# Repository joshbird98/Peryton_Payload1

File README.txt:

Team Peryton - Payload

This is internal documentation for the team, however I will publish proper open-source documentation in the future.

* For our actual flight, we opted to replace the GPS circuitry with a loud siren. This gave us a much mre reliable
and robust recovery mechanism. Whislt the hardware schematics show the GPS and LoRa system, no software has
been published.

Our payload acts as both rocket recovery mechanism, and data acquisition. It logs pressure, temperature and 9DoF
motion measurements to a microSD card, at 50 [Hz]. Power it with a LiHV cell, preferably 450mAh.
Sensors used are the BMP280 and MPU9250, many open-source libraries already exist for these ICs.
An ATMEGA328P communicates to the sensors in I2C mode, and to the microSD card in SPI mode.

As well as the hardware and software, I've also written a python script for quick analysis of flight data, useful 
for when you're still in the field. Results from our rocketry flight are also included as an example of what
the payload has achieved.

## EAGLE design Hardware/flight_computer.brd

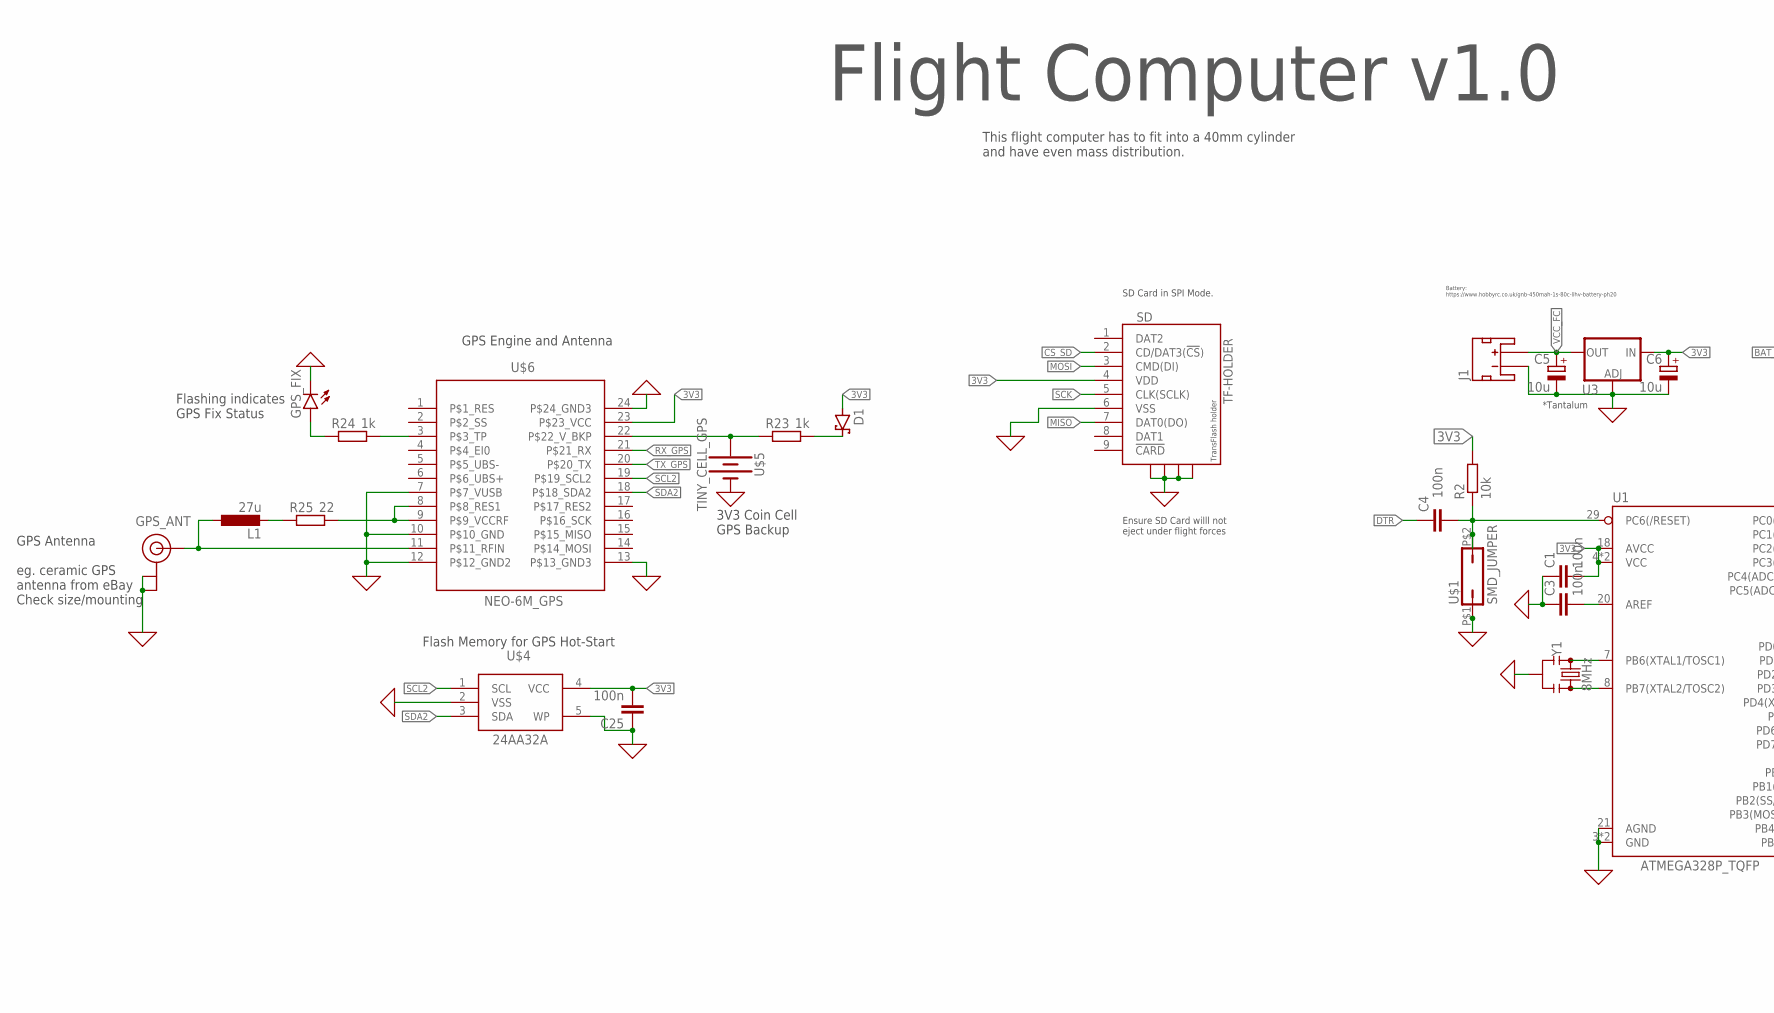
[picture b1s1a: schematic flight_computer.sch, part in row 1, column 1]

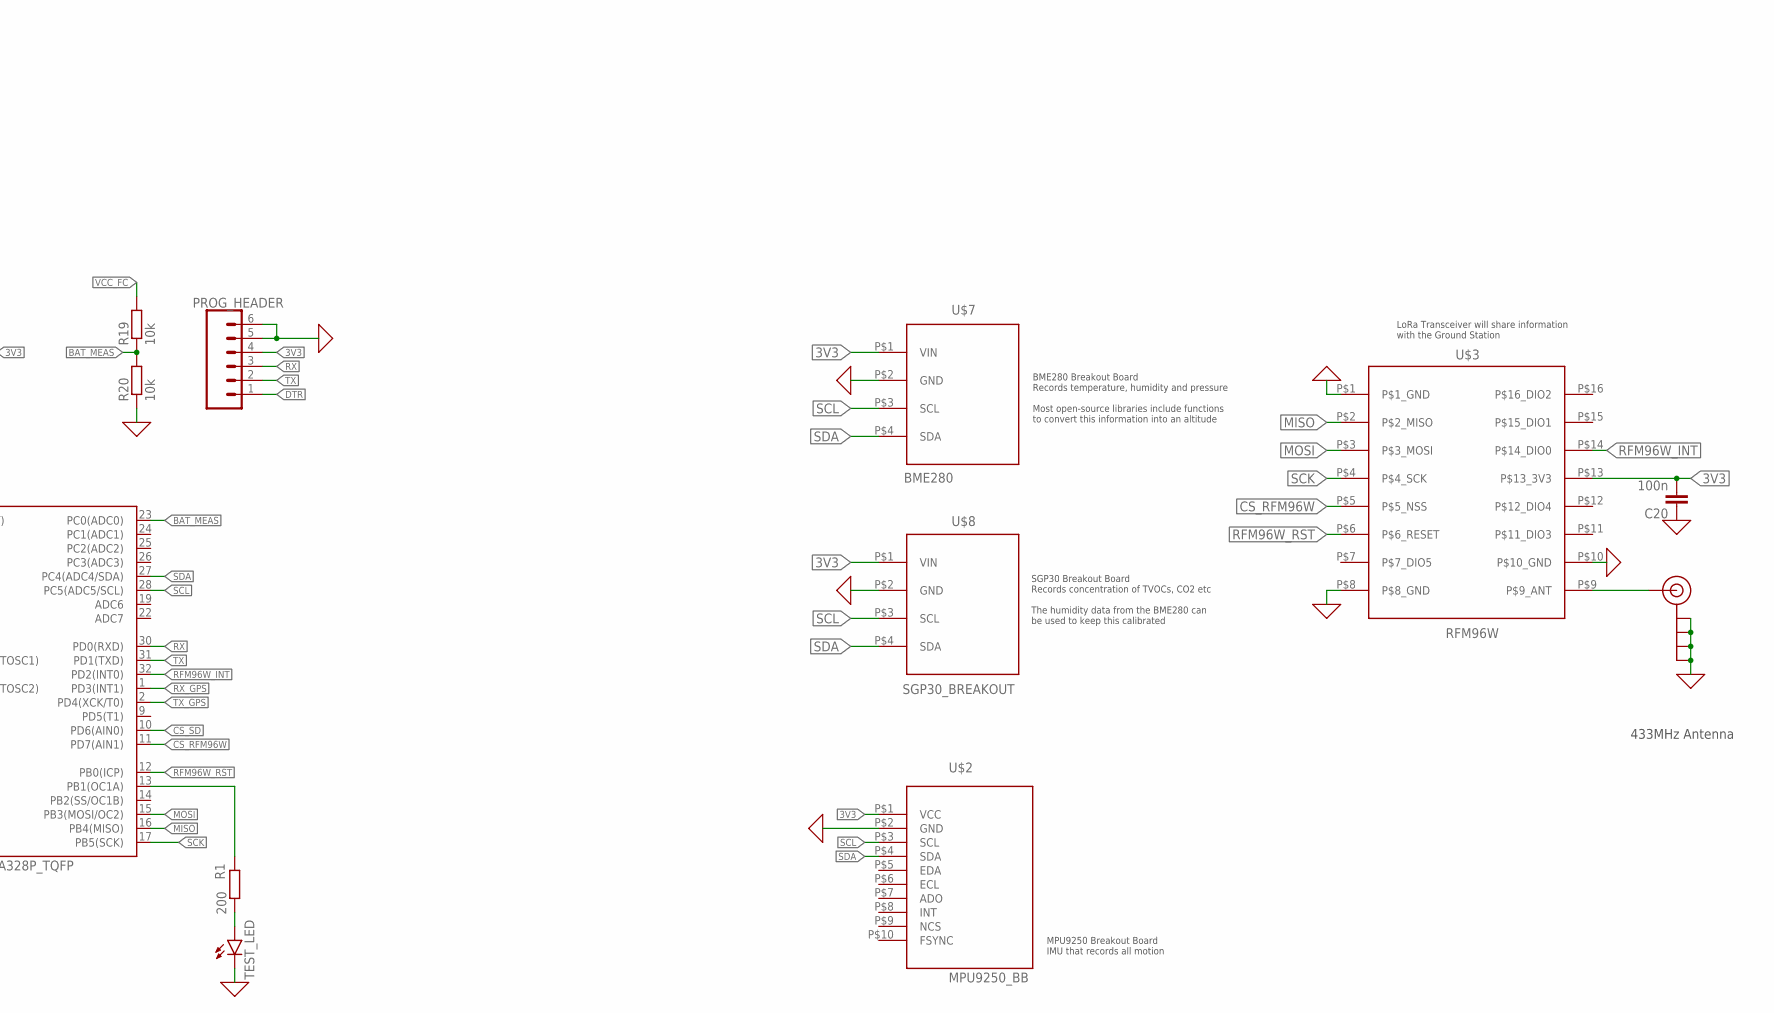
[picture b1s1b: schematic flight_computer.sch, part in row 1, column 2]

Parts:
C1, C3, C4, C20, C25: 100n; C0603
C5, C6: 10u; SMC_A
D1: 1A/40V/500mV; SOT23
GPS_ANT: U.FL
GPS_FIX: LEDCHIPLED_0603; CHIPLED_0603
J1: JST_2MM_MALE; JST-2-SMD
L1: 27u; L1812
LORA_ANT: SMA_EDGE; SMA-EDGE
PROG_HEADER: CONN_06FEMALE_LOCK; 1X06_FEMALE_LOCK.010
R1: 200; R0603
R2, R19, R20: 10k; R0603
R23, R24: 1k; R0603
R25: 22; R0603
SD: TF-HOLDER; TF-PULL
TEST_LED: LEDCHIPLED_0603; CHIPLED_0603
U1: ATMEGA328P_TQFP; TQFP32-08
U3: V_REG_LM1117SOT223; SOT223
U$1: SMD_JUMPER
U$2: MPU9250_BB
U$3: RFM96W
U$4: 24AA32A; SOT23-5L
U$5: TINY_CELL_GPS; TINY_SMD_CELL
U$6: NEO-6M_GPS; NEO-M9N/M8T/M8U
U$7: BME280; BME280_BREAKOUT
U$8: SGP30_BREAKOUT; BME280_BREAKOUT
Y1: 8MHz; RESONATOR-SMD-3.2X1.3

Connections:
0: C1.1, C3.1, C5.-, C6.-, C20.1, C25.1, GPS_ANT.1 (GND), GPS_ANT.2 (GND), GPS_FIX.C, J1.1 (-), LORA_ANT.GND@0 (GND), LORA_ANT.GND@1 (GND), LORA_ANT.GND@2 (GND), LORA_ANT.GND@3 (GND), PROG_HEADER.5, PROG_HEADER.6, R20.1, SD.6 (VSS), SD.S1, SD.S2, SD.S3, SD.S4, TEST_LED.C, U1.3 (GND), U1.5 (GND), U1.21 (AGND), U3.1 (ADJ), U$1.P$1 (1), U$2.P$2 (GND), U$3.P$1 (P$1_GND), U$3.P$8 (P$8_GND), U$3.P$10 (P$10_GND), U$4.2 (VSS), U$4.5 (WP), U$5.P$1 (-), U$6.7 (P$7_VUSB), U$6.10 (P$10_GND), U$6.12 (P$12_GND2), U$6.13 (P$13_GND3), U$6.24 (P$24_GND3), U$7.P$2 (GND), U$8.P$2 (GND), Y1.2
3V3: C1.2, C6.+, C20.2, C25.2, D1.1 (A), PROG_HEADER.4, R2.2, SD.4 (VDD), U1.4 (VCC), U1.6 (VCC), U1.18 (AVCC), U3.3 (IN), U$2.P$1 (VCC), U$3.P$13 (P$13_3V3), U$4.4 (VCC), U$6.23 (P$23_VCC), U$7.P$1 (VIN), U$8.P$1 (VIN)
BAT_MEAS: R19.1, R20.2, U1.23 (PC0(ADC0))
CS_RFM96W: U1.11 (PD7(AIN1)), U$3.P$5 (P$5_NSS)
CS_SD: SD.2 (CD/DAT3(!CS!)), U1.10 (PD6(AIN0))
DTR: C4.1, PROG_HEADER.1
MISO: SD.7 (DAT0(DO)), U1.16 (PB4(MISO)), U$3.P$2 (P$2_MISO)
MOSI: SD.3 (CMD(DI)), U1.15 (PB3(MOSI/OC2)), U$3.P$3 (P$3_MOSI)
unnamed: U1.7 (PB6(XTAL1/TOSC1)), Y1.1
unnamed: U1.8 (PB7(XTAL2/TOSC2)), Y1.3
unnamed: R1.1, U1.13 (PB1(OC1A))
unnamed: R1.2, TEST_LED.A
unnamed: C4.2, R2.1, U1.29 (PC6(/RESET)), U$1.P$2 (2)
unnamed: C3.2, U1.20 (AREF)
unnamed: LORA_ANT.SIG (SIGNAL), U$3.P$9 (P$9_ANT)
unnamed: R23.1, U$5.P$2 (+), U$6.22 (P$22_V_BKP)
unnamed: D1.3 (C), R23.2
unnamed: R24.2, U$6.3 (P$3_TP)
unnamed: GPS_FIX.A, R24.1
unnamed: R25.2, U$6.8 (P$8_RES1), U$6.9 (P$9_VCCRF)
unnamed: GPS_ANT.FEED (SIGNAL), L1.1, U$6.11 (P$11_RFIN)
unnamed: L1.2, R25.1
RFM96W_INT: U1.32 (PD2(INT0)), U$3.P$14 (P$14_DIO0)
RFM96W_RST: U1.12 (PB0(ICP)), U$3.P$6 (P$6_RESET)
RX: PROG_HEADER.3, U1.30 (PD0(RXD))
RX_GPS: U1.1 (PD3(INT1)), U$6.21 (P$21_RX)
SCK: SD.5 (CLK(SCLK)), U1.17 (PB5(SCK)), U$3.P$4 (P$4_SCK)
SCL: U1.28 (PC5(ADC5/SCL)), U$2.P$3 (SCL), U$7.P$3 (SCL), U$8.P$3 (SCL)
SCL2: U$4.1 (SCL), U$6.19 (P$19_SCL2)
SDA: U1.27 (PC4(ADC4/SDA)), U$2.P$4 (SDA), U$7.P$4 (SDA), U$8.P$4 (SDA)
SDA2: U$4.3 (SDA), U$6.18 (P$18_SDA2)
TX: PROG_HEADER.2, U1.31 (PD1(TXD))
TX_GPS: U1.2 (PD4(XCK/T0)), U$6.20 (P$20_TX)
VCC_FC: C5.+, J1.2 (+), R19.2, U3.2 (OUT), U3.4 (OUT)

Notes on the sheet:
*Tantalum
433MHz Antenna
Ensure SD Card willl not eject under flight forces
Flash Memory for GPS Hot-Start
GPS Engine and Antenna
Flashing indicates GPS Fix Status
3V3 Coin Cell GPS Backup
GPS Antenna eg. ceramic GPS antenna from eBay Check size/mounting
Battery: https://www.hobbyrc.co.uk/gnb-450mah-1s-80c-lihv-battery-ph20
SD Card in SPI Mode.
BME280 Breakout Board Records temperature, humidity and pressure Most open-source libraries include functions to convert this information into an altitude
SGP30 Breakout Board Records concentration of TVOCs, CO2 etc The humidity data from the BME280 can be used to keep this calibrated
LoRa Transceiver will share information with the Ground Station
This flight computer has to fit into a 40mm cylinder and have even mass distribution.
Flight Computer v1.0
MPU9250 Breakout Board IMU that records all motion

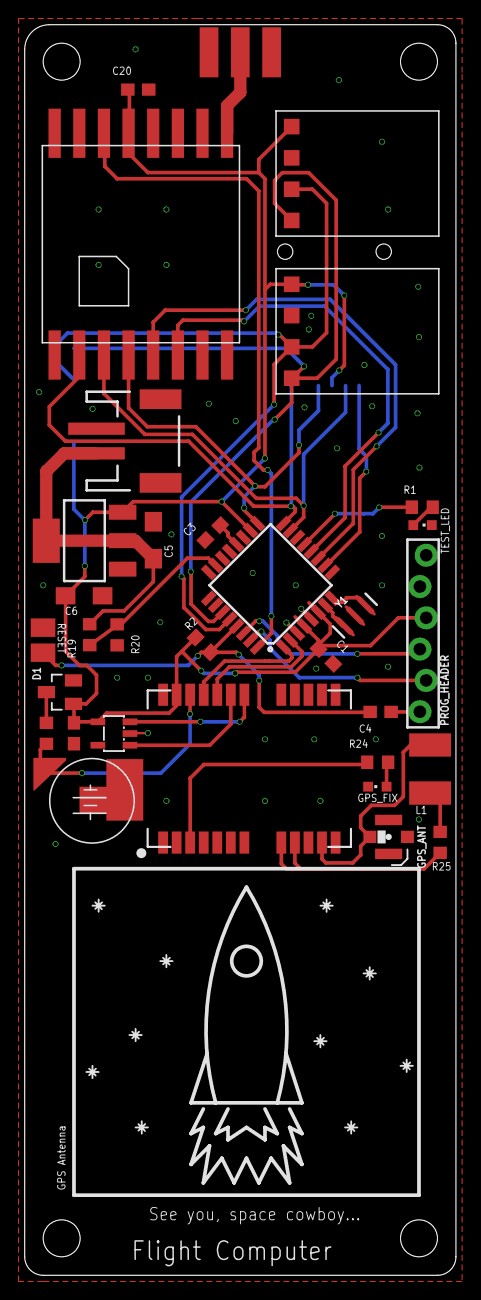
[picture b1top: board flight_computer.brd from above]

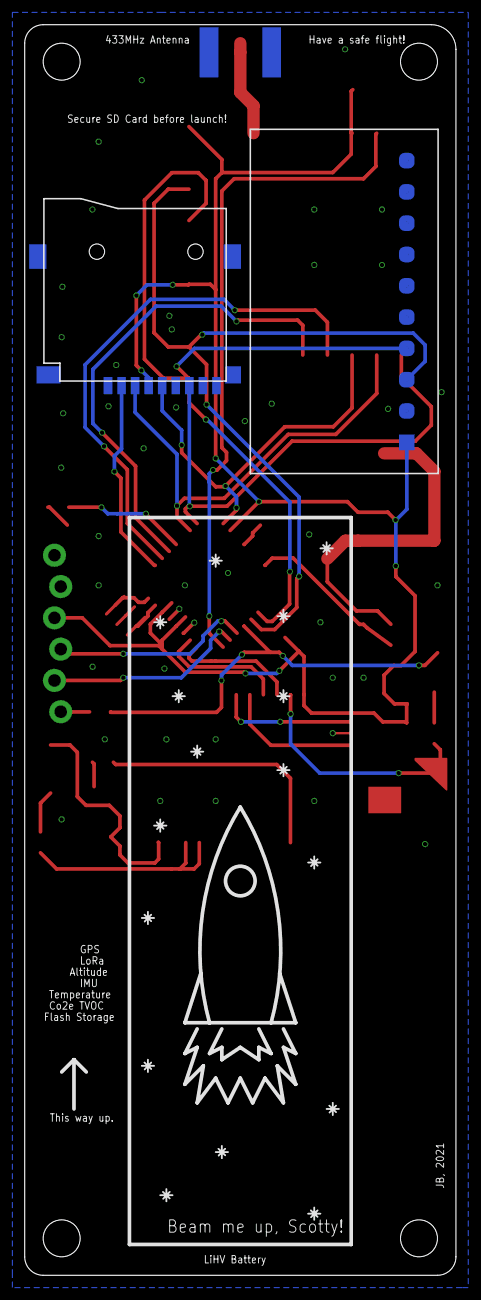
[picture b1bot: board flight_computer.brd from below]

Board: 2 copper layers, 35.0 x 101.5 mm, 34 parts (2 on the bottom side), 34 nets.

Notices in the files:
parts and their libraries:
SparkFun-Connectors: Licensing: Creative Commons ShareAlike 4.0 International - https://creativecommons.org/licenses/by-sa/4.0
